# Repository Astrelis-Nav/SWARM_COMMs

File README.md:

# SWARM_COMMs
A modular communication system for underwater ROV swarms and multi-node vehicle systems.

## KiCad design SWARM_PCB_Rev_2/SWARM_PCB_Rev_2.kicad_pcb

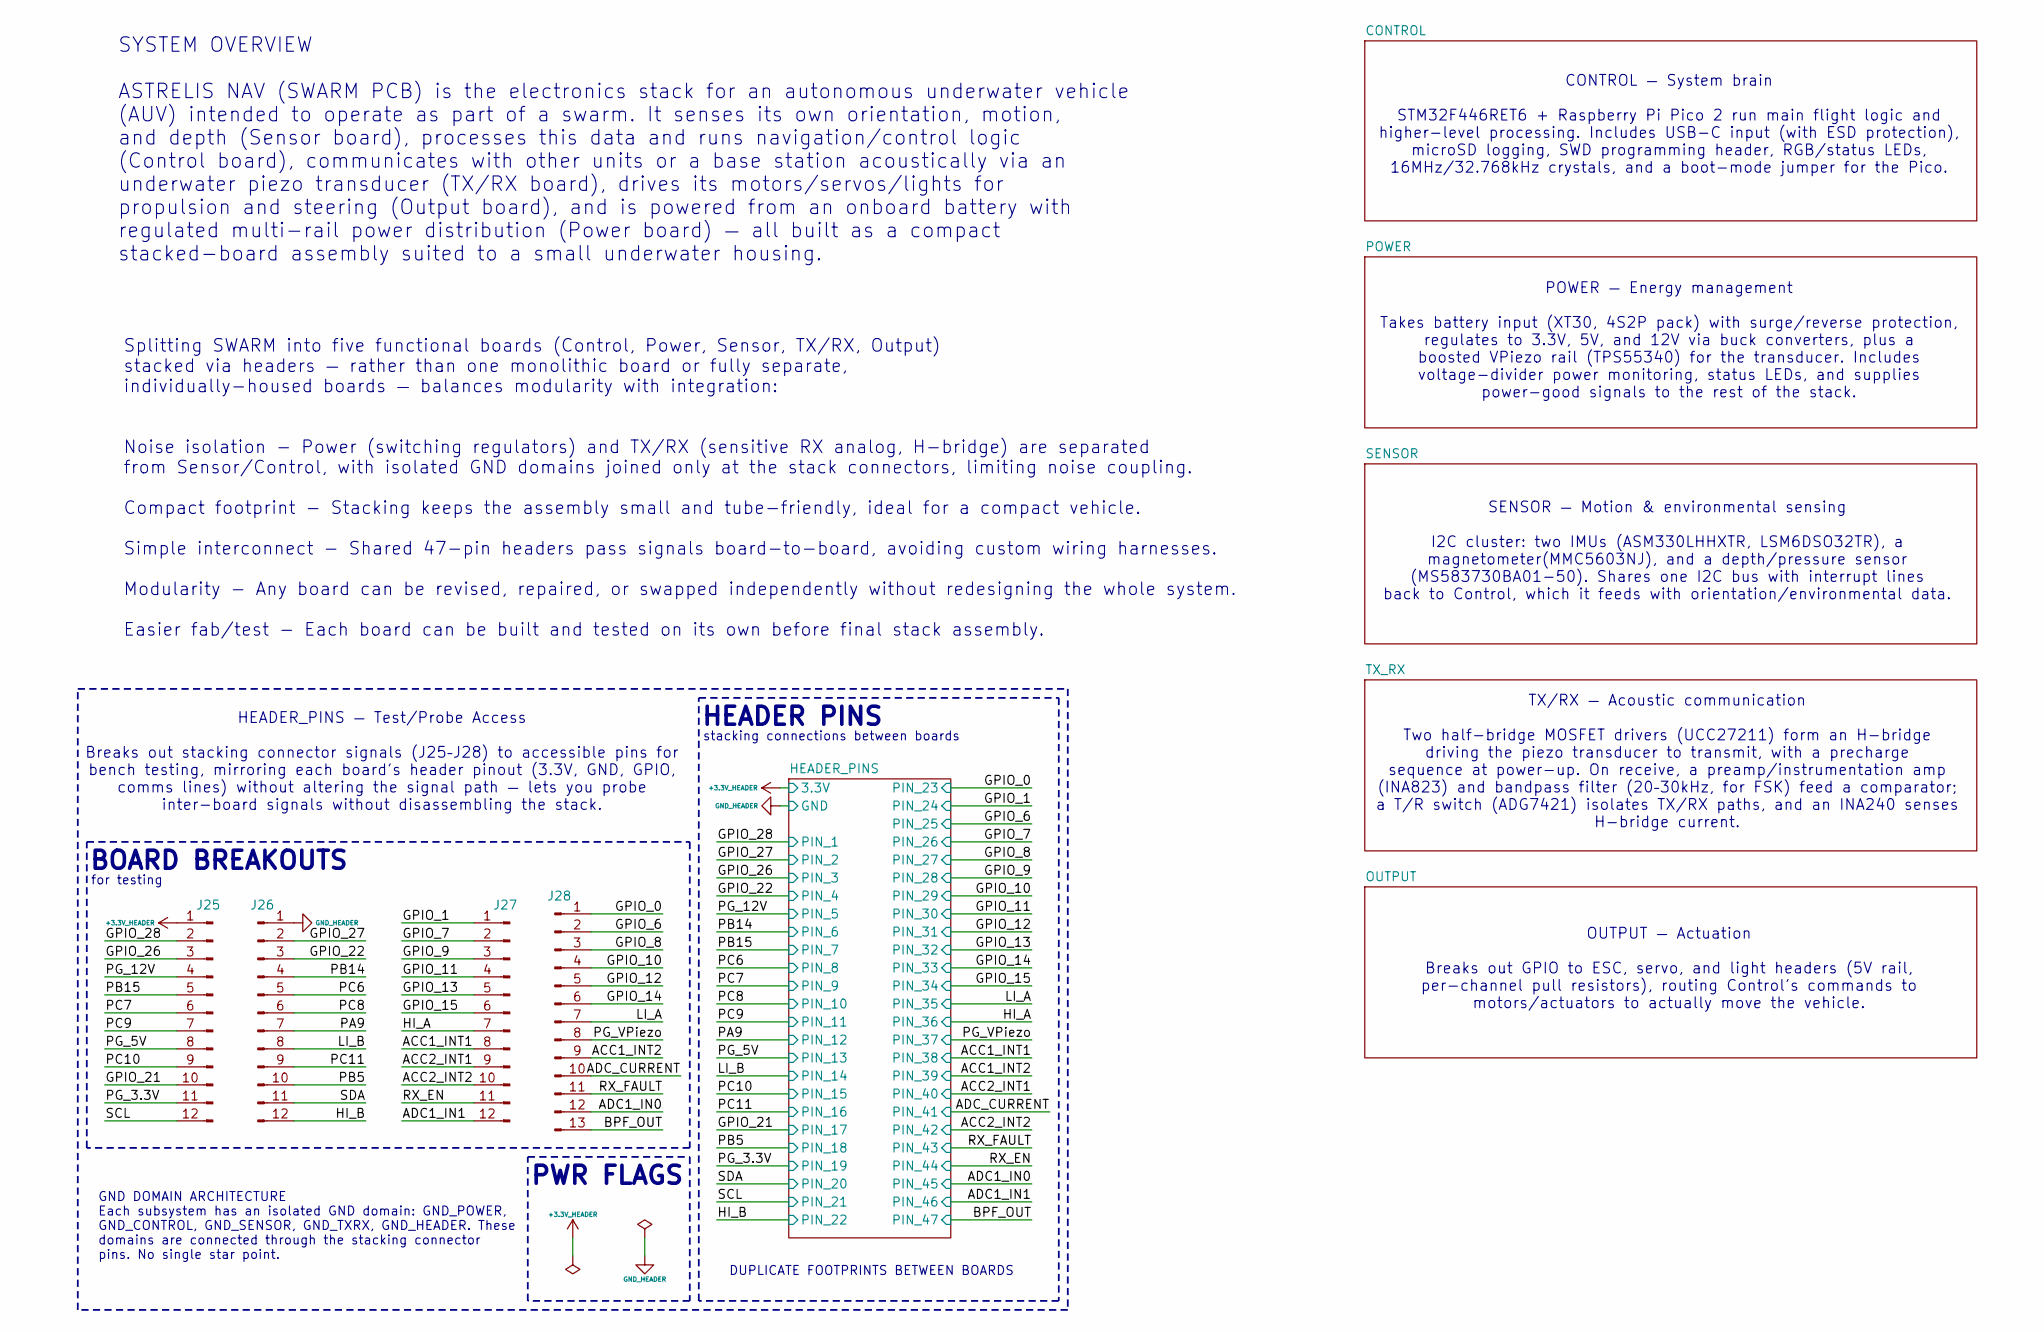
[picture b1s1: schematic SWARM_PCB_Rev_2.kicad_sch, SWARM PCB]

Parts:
J25, J26, J27: Conn_01x12_Pin; PinSocket_1x12_P2.54mm_Vertical
J28: Conn_01x13_Pin; PinSocket_1x13_P2.54mm_Vertical

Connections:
+3.3V_HEADER: J25.1; also elsewhere on the board
/ACC1_INT1: J27.8; also elsewhere on the board
/ACC1_INT2: J28.9; also elsewhere on the board
/ACC2_INT1: J27.9; also elsewhere on the board
/ACC2_INT2: J27.10; also elsewhere on the board
/ADC1_IN0: J28.12; also elsewhere on the board
/ADC1_IN1: J27.12; also elsewhere on the board
/ADC_CURRENT: J28.10; also elsewhere on the board
/BPF_OUT: J28.13; also elsewhere on the board
/GPIO_0: J28.1; also elsewhere on the board
/GPIO_1: J27.1; also elsewhere on the board
/GPIO_6: J28.2; also elsewhere on the board
/GPIO_7: J27.2; also elsewhere on the board
/GPIO_8: J28.3; also elsewhere on the board
/GPIO_9: J27.3; also elsewhere on the board
/GPIO_10: J28.4; also elsewhere on the board
/GPIO_11: J27.4; also elsewhere on the board
/GPIO_12: J28.5; also elsewhere on the board
/GPIO_13: J27.5; also elsewhere on the board
/GPIO_14: J28.6; also elsewhere on the board
/GPIO_15: J27.6; also elsewhere on the board
/GPIO_21: J25.10; also elsewhere on the board
/GPIO_22: J26.3; also elsewhere on the board
/GPIO_26: J25.3; also elsewhere on the board
/GPIO_27: J26.2; also elsewhere on the board
/GPIO_28: J25.2; also elsewhere on the board
/HI_A: J27.7; also elsewhere on the board
/HI_B: J26.12; also elsewhere on the board
/LI_A: J28.7; also elsewhere on the board
/LI_B: J26.8; also elsewhere on the board
/PA9: J26.7; also elsewhere on the board
/PB5: J26.10; also elsewhere on the board
/PB14: J26.4; also elsewhere on the board
/PB15: J25.5; also elsewhere on the board
/PC6: J26.5; also elsewhere on the board
/PC7: J25.6; also elsewhere on the board
/PC8: J26.6; also elsewhere on the board
/PC9: J25.7; also elsewhere on the board
/PC10: J25.9; also elsewhere on the board
/PC11: J26.9; also elsewhere on the board
/PG_3.3V: J25.11; also elsewhere on the board
/PG_5V: J25.8; also elsewhere on the board
/PG_12V: J25.4; also elsewhere on the board
/PG_VPiezo: J28.8; also elsewhere on the board
/RX_EN: J27.11; also elsewhere on the board
/RX_FAULT: J28.11; also elsewhere on the board
/SCL: J25.12; also elsewhere on the board
/SDA: J26.11; also elsewhere on the board
GND_HEADER: J26.1; also elsewhere on the board

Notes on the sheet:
SYSTEM OVERVIEW ASTRELIS NAV (SWARM PCB) is the electronics stack for an autonomous underwater vehicle (AUV) intended to operate as part of a swarm. It senses its own orientation, motion, and depth (Sensor board), processes this data and runs navigation/control logic (Control board), communicates w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
for testing
DUPLICATE FOOTPRINTS BETWEEN BOARDS
HEADER_PINS — Test/Probe Access Breaks out stacking connector signals (J25–J28) to accessible pins for bench testing, mirroring each board's header pinout (3.3V, GND, GPIO, comms lines) without altering the signal path — lets you probe inter-board signals without disassembling the stack.
SENSOR — Motion & environmental sensing I2C cluster: two IMUs (ASM330LHHXTR, LSM6DSO32TR), a magnetometer(MMC5603NJ), and a depth/pressure sensor (MS583730BA01-50). Shares one I2C bus with interrupt lines back to Control, which it feeds with orientation/environmental data.
Splitting SWARM into five functional boards (Control, Power, Sensor, TX/RX, Output) stacked via headers — rather than one monolithic board or fully separate, individually-housed boards — balances modularity with integration: Noise isolation - Power (switching regulators) and TX/RX (sensitive RX ana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
POWER — Energy management Takes battery input (XT30, 4S2P pack) with surge/reverse protection, regulates to 3.3V, 5V, and 12V via buck converters, plus a boosted VPiezo rail (TPS55340) for the transducer. Includes voltage-divider power monitoring, status LEDs, and supplies power-good signals to the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
stacking connections between boards
BOARD BREAKOUTS
GND DOMAIN ARCHITECTURE Each subsystem has an isolated GND domain: GND_POWER, GND_CONTROL, GND_SENSOR, GND_TXRX, GND_HEADER. These domains are connected through the stacking connector pins. No single star point.
OUTPUT — Actuation Breaks out GPIO to ESC, servo, and light headers (5V rail, per-channel pull resistors), routing Control's commands to motors/actuators to actually move the vehicle.
CONTROL — System brain STM32F446RET6 + Raspberry Pi Pico 2 run main flight logic and higher-level processing. Includes USB-C input (with ESD protection), microSD logging, SWD programming header, RGB/status LEDs, 16MHz/32.768kHz crystals, and a boot-mode jumper for the Pico.
TX/RX — Acoustic communication Two half-bridge MOSFET drivers (UCC27211) form an H-bridge driving the piezo transducer to transmit, with a precharge sequence at power-up. On receive, a preamp/instrumentation amp (INA823) and bandpass filter (20–30kHz, for FSK) feed a comparator; a T/R switch (ADG74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
HEADER PINS
PWR FLAGS

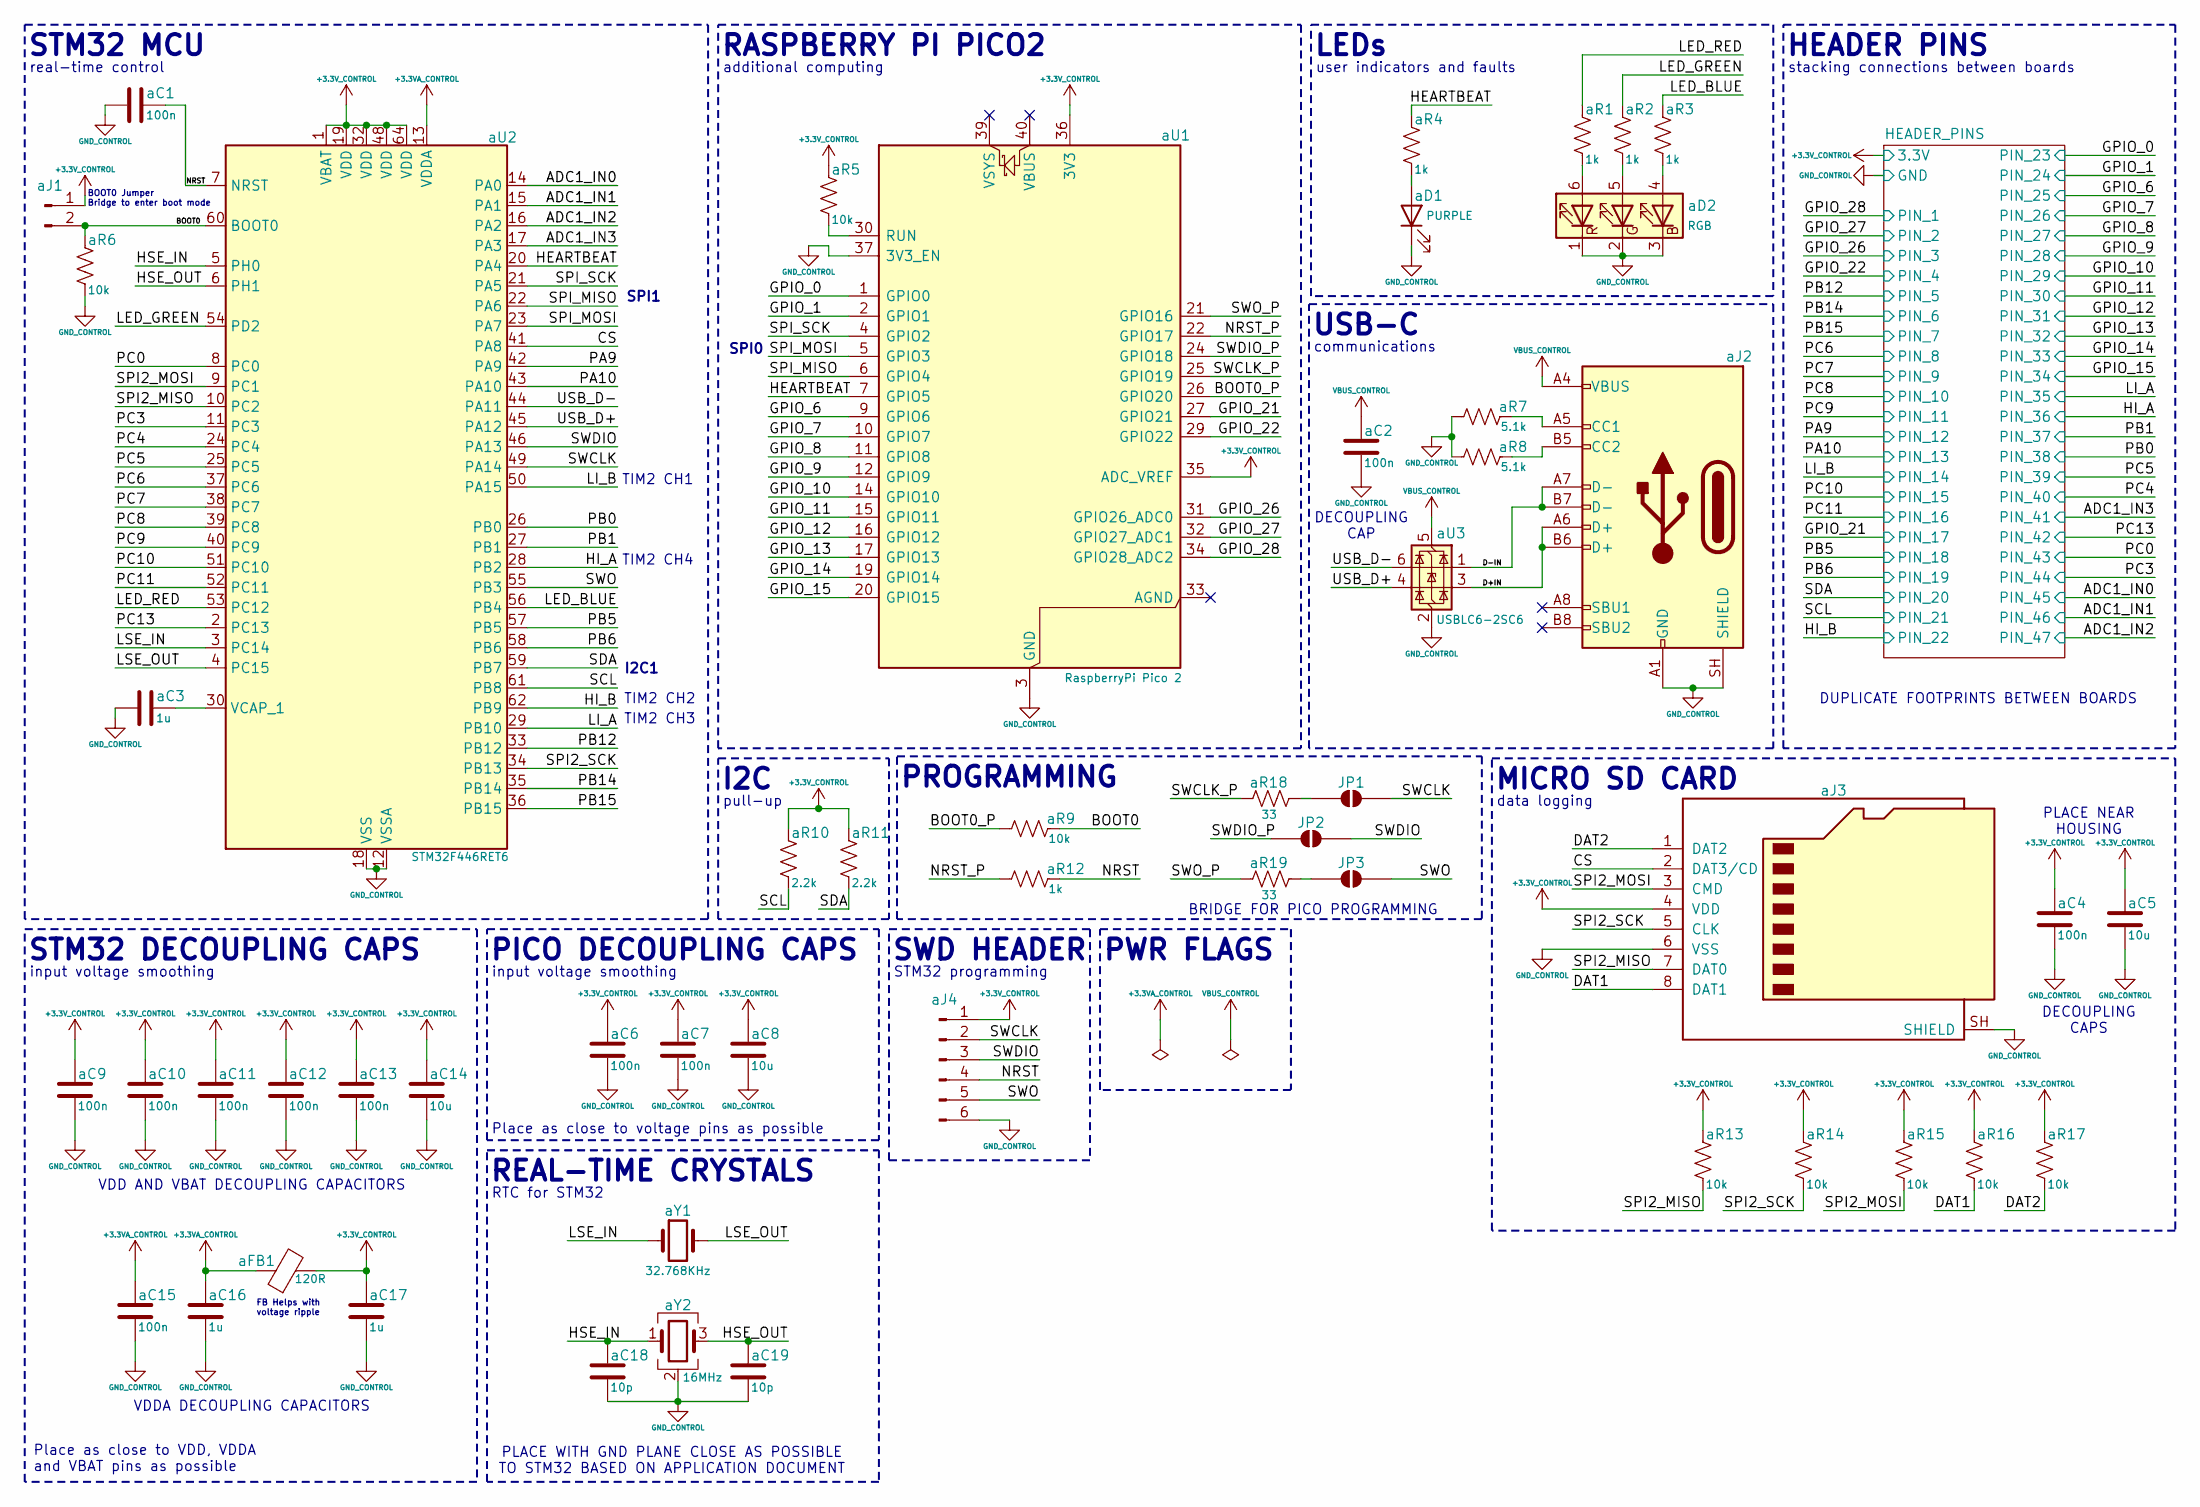
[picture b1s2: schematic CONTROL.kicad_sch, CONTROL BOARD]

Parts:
JP1, JP2, JP3: SolderJumper_2_Open; SolderJumper-2_P1.3mm_Open_TrianglePad1.0x1.5mm
aC1, aC2, aC4, aC6, aC7, aC9, aC10, aC11, aC12, aC13, aC15: 100n; C_0603_1608Metric; MPN GRM188R71C104KA01D
aC3: 1u; C_0603_1608Metric; MPN GRM188R60J105KE15D
aC5, aC8, aC14: 10u; C_0603_1608Metric; MPN GRM188R60J106ME47D
aC16, aC17: 1u; C_0603_1608Metric; MPN GRM188R61A105KA61D
aC18, aC19: 10p; C_0603_1608Metric; MPN GRM1885C1H100JA01D
aD1: PURPLE; LED_JE2835_CRW
aD2: RGB; LED_RGB_PLCC-6
aFB1: 120R; R_0603_1608Metric; MPN BLM18BD121SN1D
aJ1: Conn_01x02_Pin; PinHeader_1x02_P1.00mm_Vertical
aJ2: USB_C_Receptacle_USB2.0_16P; USB_C_Receptacle_GCT_USB4085; MPN USB4085-GF-A
aJ3: Micro_SD_Card; AMPHENOL_1140084168; MPN 1140084168
aJ4: Conn_01x06_Pin; PinHeader_1x06_P1.00mm_Vertical
aR1, aR2, aR3, aR4, aR12: 1k; R_0603_1608Metric; MPN RC0603FR-071KL
aR5, aR6, aR9, aR13, aR14, aR15, aR16, aR17: 10k; R_0603_1608Metric; MPN RC0603FR-0710KL
aR7, aR8: 5.1k; R_0603_1608Metric; MPN RC0603FR-075K1L
aR10, aR11: 2.2k; R_0603_1608Metric; MPN RC0603FR-074K7L
aR18, aR19: 33; R_0603_1608Metric; MPN RC0603FR-0733RL
aU1: RaspberryPi Pico 2; RaspberryPi_Pico_SMD; MPN SC0918
aU2: STM32F446RET6; LQFP-64_10x10mm_P0.5mm; MPN STM32F446RET6
aU3: USBLC6-2SC6; SOT-23-6; MPN USBLC6-2SC6
aY1: 32.768KHz; Crystal_SMD_MicroCrystal_CM9V-T1A-2Pin_1.6x1.0mm; MPN CM9V-T1A-32.768KDZB-UT
aY2: 16MHz; Crystal_SMD_SeikoEpson_FA238-4Pin_3.2x2.5mm; MPN FA-238 16.0000MB

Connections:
+3.3VA_CONTROL: aC15.2, aC16.2, aFB1.1, aU2.13 (VDDA)
+3.3V_CONTROL: aC4.2, aC5.2, aC6.2, aC7.2, aC8.2, aC9.2, aC10.2, aC11.2, aC12.2, aC13.2, aC14.2, aC17.2, aFB1.2, aJ1.1, aJ3.4 (VDD), aJ4.1, aR5.2, aR10.2, aR11.2, aR13.2, aR14.2, aR15.2, aR16.2, aR17.2, aU1.35 (ADC_VREF), aU1.36 (3V3), aU2.1 (VBAT), aU2.19 (VDD), aU2.32 (VDD), aU2.48 (VDD), aU2.64 (VDD); also elsewhere on the board
/CONTROL/ADC1_IN0: aU2.14 (PA0); also elsewhere on the board
/CONTROL/ADC1_IN1: aU2.15 (PA1); also elsewhere on the board
/CONTROL/ADC1_IN2: aU2.16 (PA2); also elsewhere on the board
/CONTROL/ADC1_IN3: aU2.17 (PA3); also elsewhere on the board
/CONTROL/BOOT0: aJ1.2, aR6.2, aR9.1, aU2.60 (BOOT0)
/CONTROL/BOOT0_P: aR9.2, aU1.26 (GPIO20)
/CONTROL/CS: aJ3.2 (DAT3/CD), aU2.41 (PA8)
/CONTROL/D+IN: aJ2.A6 (D+), aJ2.B6 (D+), aU3.3 (I/O2)
/CONTROL/D-IN: aJ2.A7 (D-), aJ2.B7 (D-), aU3.1 (I/O1)
/CONTROL/DAT1: aJ3.8 (DAT1), aR16.1
/CONTROL/DAT2: aJ3.1 (DAT2), aR17.1
/CONTROL/GPIO_0: aU1.1 (GPIO0); also elsewhere on the board
/CONTROL/GPIO_1: aU1.2 (GPIO1); also elsewhere on the board
/CONTROL/GPIO_6: aU1.9 (GPIO6); also elsewhere on the board
/CONTROL/GPIO_7: aU1.10 (GPIO7); also elsewhere on the board
/CONTROL/GPIO_8: aU1.11 (GPIO8); also elsewhere on the board
/CONTROL/GPIO_9: aU1.12 (GPIO9); also elsewhere on the board
/CONTROL/GPIO_10: aU1.14 (GPIO10); also elsewhere on the board
/CONTROL/GPIO_11: aU1.15 (GPIO11); also elsewhere on the board
/CONTROL/GPIO_12: aU1.16 (GPIO12); also elsewhere on the board
/CONTROL/GPIO_13: aU1.17 (GPIO13); also elsewhere on the board
/CONTROL/GPIO_14: aU1.19 (GPIO14); also elsewhere on the board
/CONTROL/GPIO_15: aU1.20 (GPIO15); also elsewhere on the board
/CONTROL/GPIO_21: aU1.27 (GPIO21); also elsewhere on the board
/CONTROL/GPIO_22: aU1.29 (GPIO22); also elsewhere on the board
/CONTROL/GPIO_26: aU1.31 (GPIO26_ADC0); also elsewhere on the board
/CONTROL/GPIO_27: aU1.32 (GPIO27_ADC1); also elsewhere on the board
/CONTROL/GPIO_28: aU1.34 (GPIO28_ADC2); also elsewhere on the board
/CONTROL/HEARTBEAT: aR4.2, aU1.7 (GPIO5), aU2.20 (PA4)
/CONTROL/HI_A: aU2.28 (PB2); also elsewhere on the board
/CONTROL/HI_B: aU2.62 (PB9); also elsewhere on the board
/CONTROL/HSE_IN: aC18.2, aU2.5 (PH0), aY2.1
/CONTROL/HSE_OUT: aC19.2, aU2.6 (PH1), aY2.3
/CONTROL/LED_BLUE: aR3.2, aU2.56 (PB4)
/CONTROL/LED_GREEN: aR2.2, aU2.54 (PD2)
/CONTROL/LED_RED: aR1.2, aU2.53 (PC12)
/CONTROL/LI_A: aU2.29 (PB10); also elsewhere on the board
/CONTROL/LI_B: aU2.50 (PA15); also elsewhere on the board
/CONTROL/LSE_IN: aU2.3 (PC14), aY1.1
/CONTROL/LSE_OUT: aU2.4 (PC15), aY1.2
/CONTROL/NRST: aC1.2, aJ4.4, aR12.1, aU2.7 (NRST)
/CONTROL/NRST_P: aR12.2, aU1.22 (GPIO17)
/CONTROL/PA9: aU2.42 (PA9); also elsewhere on the board
/CONTROL/PA10: aU2.43 (PA10); also elsewhere on the board
/CONTROL/PB0: aU2.26 (PB0); also elsewhere on the board
/CONTROL/PB1: aU2.27 (PB1); also elsewhere on the board
/CONTROL/PB5: aU2.57 (PB5); also elsewhere on the board
/CONTROL/PB6: aU2.58 (PB6); also elsewhere on the board
/CONTROL/PB12: aU2.33 (PB12); also elsewhere on the board
/CONTROL/PB14: aU2.35 (PB14); also elsewhere on the board
/CONTROL/PB15: aU2.36 (PB15); also elsewhere on the board
/CONTROL/PC0: aU2.8 (PC0); also elsewhere on the board
/CONTROL/PC3: aU2.11 (PC3); also elsewhere on the board
/CONTROL/PC4: aU2.24 (PC4); also elsewhere on the board
/CONTROL/PC5: aU2.25 (PC5); also elsewhere on the board
/CONTROL/PC6: aU2.37 (PC6); also elsewhere on the board
/CONTROL/PC7: aU2.38 (PC7); also elsewhere on the board
/CONTROL/PC8: aU2.39 (PC8); also elsewhere on the board
/CONTROL/PC9: aU2.40 (PC9); also elsewhere on the board
/CONTROL/PC10: aU2.51 (PC10); also elsewhere on the board
/CONTROL/PC11: aU2.52 (PC11); also elsewhere on the board
/CONTROL/PC13: aU2.2 (PC13); also elsewhere on the board
/CONTROL/SCL: aR10.1, aU2.61 (PB8); also elsewhere on the board
/CONTROL/SDA: aR11.1, aU2.59 (PB7); also elsewhere on the board
/CONTROL/SPI2_MISO: aJ3.7 (DAT0), aR13.1, aU2.10 (PC2)
/CONTROL/SPI2_MOSI: aJ3.3 (CMD), aR15.1, aU2.9 (PC1)
/CONTROL/SPI2_SCK: aJ3.5 (CLK), aR14.1, aU2.34 (PB13)
/CONTROL/SPI_MISO: aU1.6 (GPIO4), aU2.22 (PA6)
/CONTROL/SPI_MOSI: aU1.5 (GPIO3), aU2.23 (PA7)
/CONTROL/SPI_SCK: aU1.4 (GPIO2), aU2.21 (PA5)
/CONTROL/SWCLK: JP1.2 (B), aJ4.2, aU2.49 (PA14)
/CONTROL/SWCLK_P: aR18.2, aU1.25 (GPIO19)
/CONTROL/SWDIO: JP2.2 (B), aJ4.3, aU2.46 (PA13)
/CONTROL/SWDIO_P: JP2.1 (A), aU1.24 (GPIO18)
/CONTROL/SWO: JP3.2 (B), aJ4.5, aU2.55 (PB3)
/CONTROL/SWO_P: aR19.2, aU1.21 (GPIO16)
/CONTROL/USB_D+: aU2.45 (PA12), aU3.4 (I/O2)
/CONTROL/USB_D-: aU2.44 (PA11), aU3.6 (I/O1)
GND_CONTROL: aC1.1, aC2.1, aC3.1, aC4.1, aC5.1, aC6.1, aC7.1, aC8.1, aC9.1, aC10.1, aC11.1, aC12.1, aC13.1, aC14.1, aC15.1, aC16.1, aC17.1, aC18.1, aC19.1, aD1.1 (K), aD2.1 (RK), aD2.2 (GK), aD2.3 (BK), aJ2.A1 (GND), aJ2.A12 (GND), aJ2.B1 (GND), aJ2.B12 (GND), aJ2.SH (SHIELD), aJ3.6 (VSS), aJ3.SH (SHIELD), aJ4.6, aR6.1, aR7.2, aR8.2, aU1.3 (GND), aU1.8 (GND), aU1.13 (GND), aU1.18 (GND), aU1.23 (GND), aU1.28 (GND), aU1.37 (3V3_EN), aU1.38 (GND), aU2.12 (VSSA), aU2.18 (VSS), aU2.31 (VSS), aU2.47 (VSS), aU2.63 (VSS), aU3.2 (GND), aY2.2 (G), aY2.4 (G); also elsewhere on the board
unnamed: JP1.1 (A), aR18.1
unnamed: JP3.1 (A), aR19.1
unnamed: aD1.2 (A), aR4.1
unnamed: aD2.4 (BA), aR3.1
unnamed: aD2.5 (GA), aR2.1
unnamed: aD2.6 (RA), aR1.1
unnamed: aJ2.A5 (CC1), aR7.1
unnamed: aJ2.B5 (CC2), aR8.1
unnamed: aR5.1, aU1.30 (RUN)
unnamed: aC3.2, aU2.30 (VCAP_1)
VBUS_CONTROL: aC2.2, aJ2.A4 (VBUS), aJ2.A9 (VBUS), aJ2.B4 (VBUS), aJ2.B9 (VBUS), aU3.5 (VBUS)

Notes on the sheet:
DECOUPLING CAP
VDDA DECOUPLING CAPACITORS
user indicators and faults
real-time control
DECOUPLING CAPS
Place as close to voltage pins as possible
data logging
FB Helps with voltage ripple
STM32 MCU
BOOT0 Jumper Bridge to enter boot mode
SPI1
BRIDGE FOR PICO PROGRAMMING
STM32 programming
communications
Place as close to VDD, VDDA and VBAT pins as possible
USB-C
I2C
STM32 DECOUPLING CAPS
TIM2 CH3
PLACE WITH GND PLANE CLOSE AS POSSIBLE TO STM32 BASED ON APPLICATION DOCUMENT
PLACE NEAR HOUSING
SWD HEADER
additional computing
PWR FLAGS
input voltage smoothing
RTC for STM32
LEDs
TIM2 CH4
VDD AND VBAT DECOUPLING CAPACITORS
SPI0
HEADER PINS
I2C1
MICRO SD CARD
TIM2 CH2
PROGRAMMING
pull-up
RASPBERRY PI PICO2
stacking connections between boards
PICO DECOUPLING CAPS
TIM2 CH1

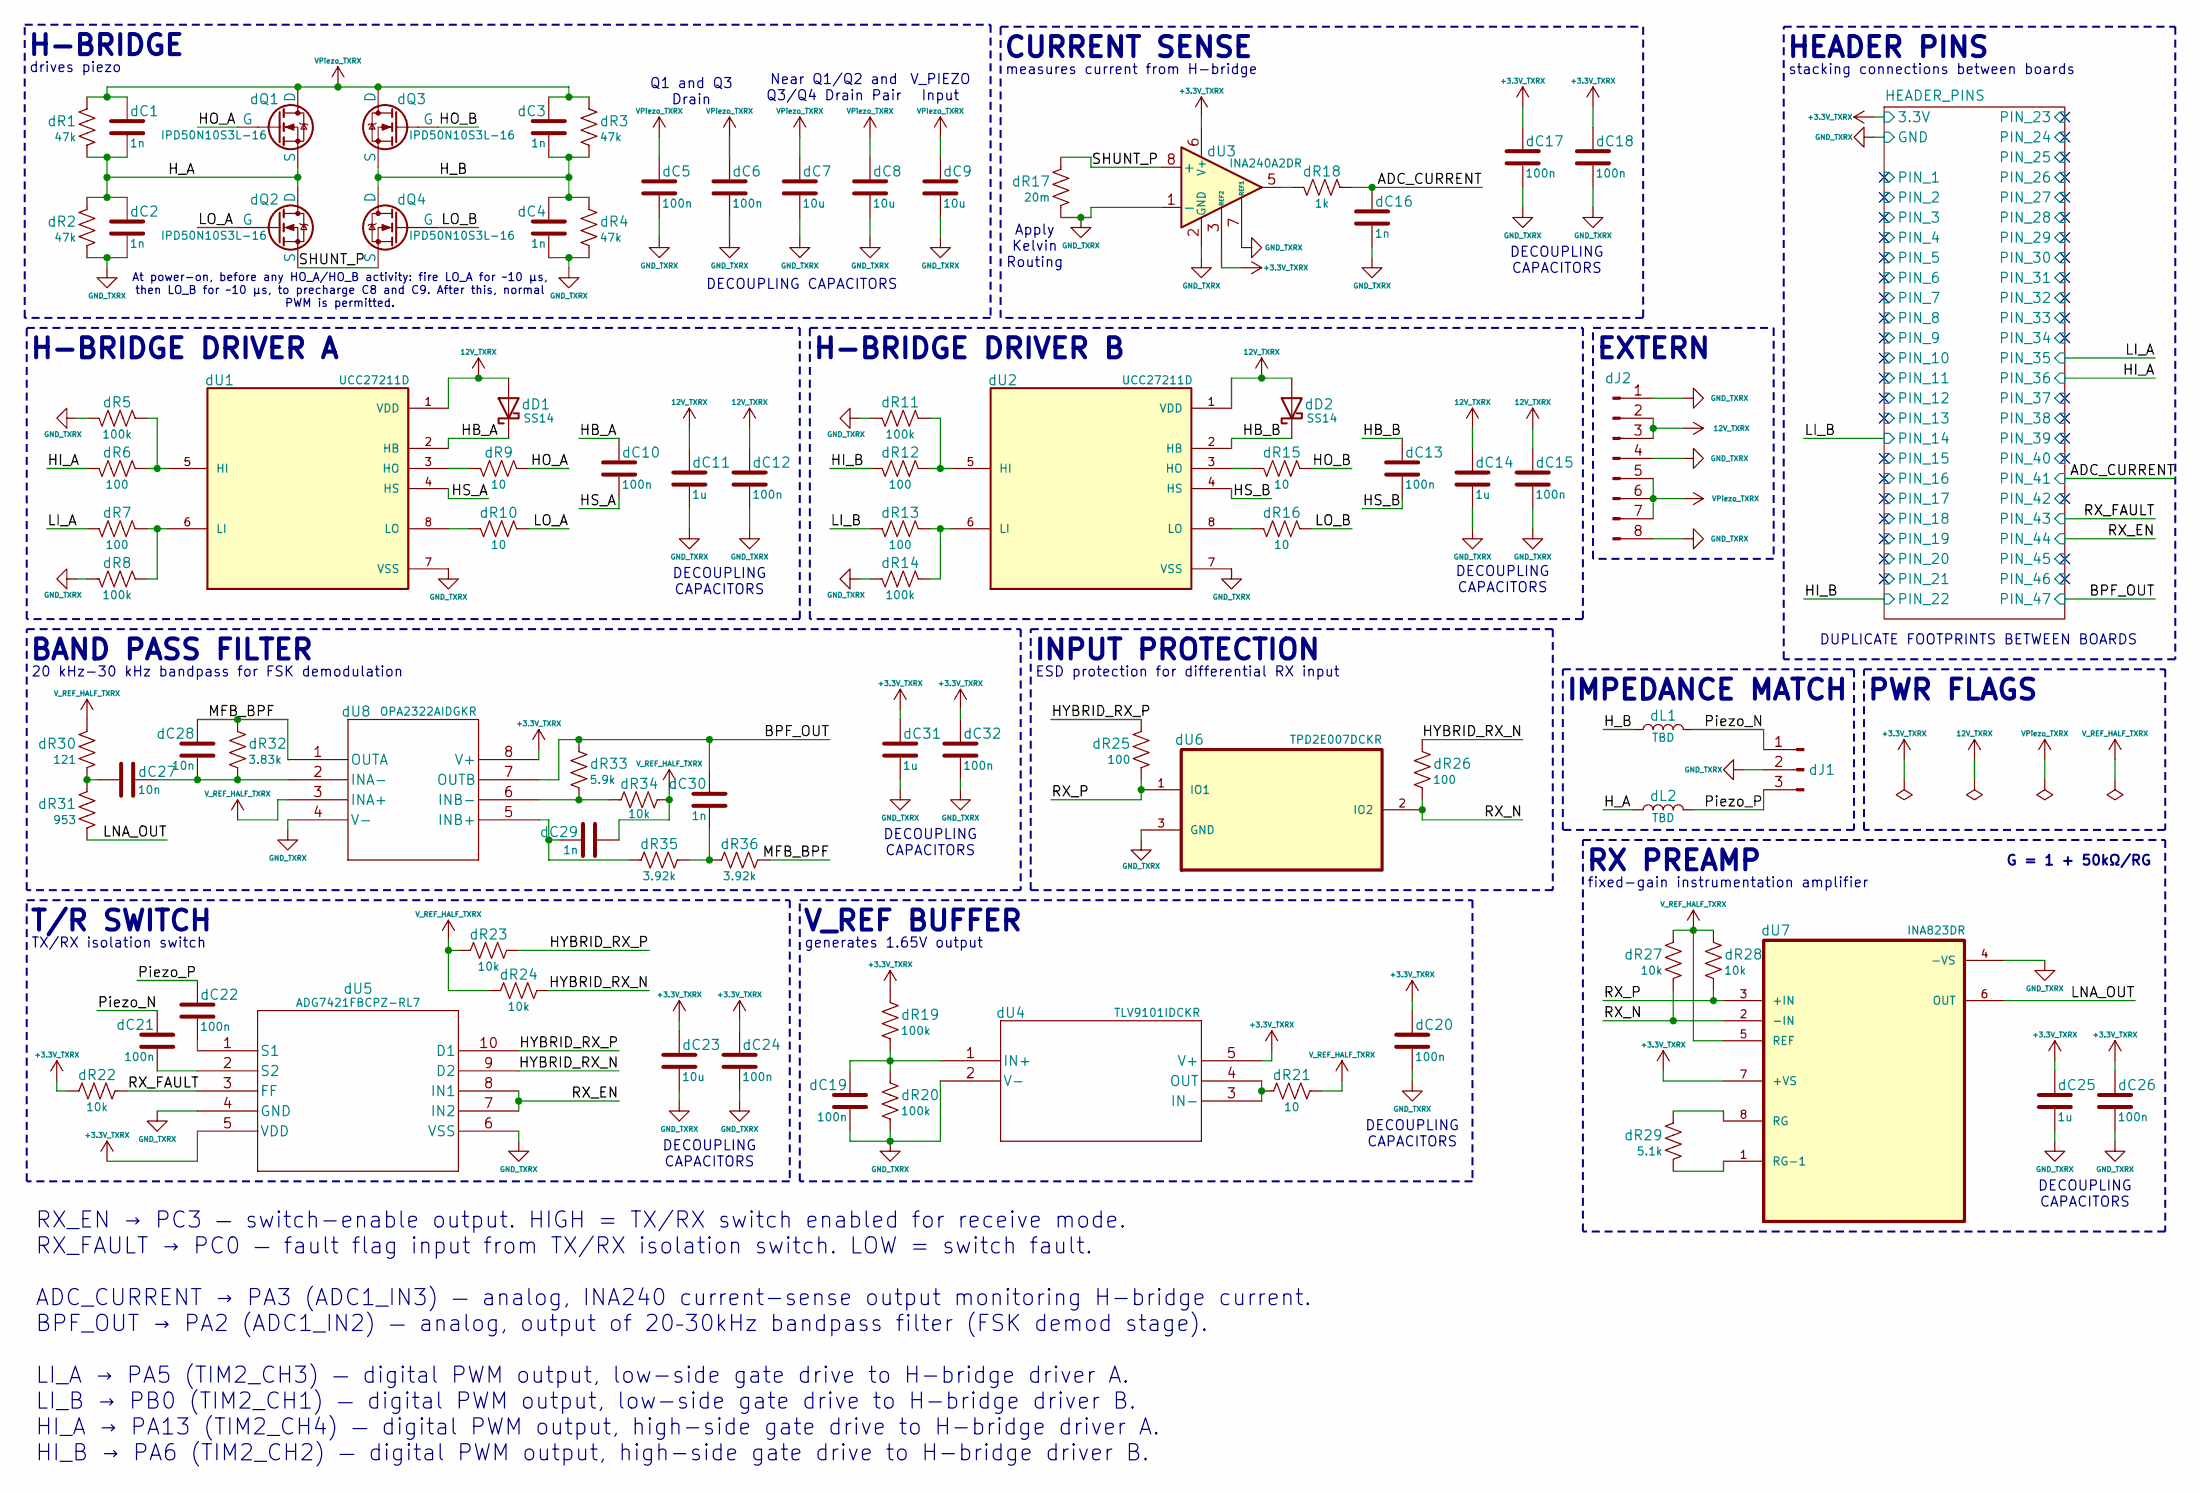
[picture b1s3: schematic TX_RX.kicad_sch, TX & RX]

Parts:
dC1, dC2, dC3, dC4, dC16, dC29, dC30: 1n; C_0603_1608Metric; MPN GRM1885C1H102JA01D
dC5, dC6, dC10, dC12, dC13, dC15, dC17, dC18, dC19, dC20, dC21, dC22, dC24, dC26, dC32: 100n; C_0603_1608Metric; MPN GRM188R71C104KA01D
dC7, dC8, dC9: 10u; C_1210_3225Metric; MPN GRM32ER71H106KA12
dC11, dC14: 1u; C_0805_2012Metric; MPN GRM21BR61A105KA73L
dC23: 10u; C_0805_2012Metric_Pad1.18x1.45mm_HandSolder; MPN GRM21BR61A106KE18L
dC25, dC31: 1u; C_0603_1608Metric; MPN GRM188R61A105KA61D
dC27, dC28: 10n; C_0603_1608Metric; MPN GRM188R71H103KA01D
dD1, dD2: SS14; D_SMA
dJ1: Conn_01x03_Pin; JST_XH_B3B-XH-AM_1x03_P2.50mm_Vertical; MPN B3B-XH-AM
dJ2: Conn_01x08_Pin; JST_PH_B8B-PH-SM4-TB_1x08-1MP_P2.00mm_Vertical; MPN B8B-PH-SM4-TB(LF)(SN)
dL1, dL2: TBD; L_Panasonic_PCC-M0630M
dQ1, dQ2, dQ3, dQ4: IPD50N10S3L-16; TO-252-2; MPN IPD50N10S3L-16
dR1, dR2, dR3, dR4: 47k; R_0603_1608Metric; MPN RC0603FR-0747KL
dR5, dR8, dR11, dR14, dR19, dR20: 100k; R_0603_1608Metric; MPN RC0603FR-07100KL
dR6, dR7, dR12, dR13, dR25, dR26: 100; R_0603_1608Metric; MPN RC0603FR-07100RL
dR9, dR10, dR15, dR16, dR21: 10; R_0603_1608Metric; MPN RC0603FR-0710RL
dR17: 20m; R_2512_6332Metric; MPN WSL2512R0200FEA
dR18: 1k; R_0603_1608Metric; MPN RC0603FR-071KL
dR22, dR23, dR24, dR27, dR28, dR34: 10k; R_0603_1608Metric; MPN RC0603FR-0710KL
dR29: 5.1k; R_0603_1608Metric; MPN RC0603FR-075K1L
dR30: 121; R_0603_1608Metric; MPN RC0603FR-07121RL
dR31: 953; R_0603_1608Metric; MPN RC0603FR-07953RL
dR32: 3.83k; R_0603_1608Metric; MPN RC0603FR-073K83L
dR33: 5.9k; R_0603_1608Metric; MPN RC0603FR-075K9L
dR35, dR36: 3.92k; R_0603_1608Metric; MPN RC0603FR-073K92L
dU1, dU2: UCC27211D; SOIC127P599X175-8N; PARTREV F; DigiKey_Part_Number 296-30016-5-ND
dU3: INA240A2DR; SOIC-8_3.9x4.9mm_P1.27mm; MPN INA240A2DR
dU4: TLV9101IDCKR; SC70-5_DCK_TEX; MPN TLV9101IDCKR
dU5: ADG7421FBCPZ-RL7; CP-10-16_ADI; MPN ADG7421FBCPZ-RL7
dU6: TPD2E007DCKR; DCK3; MPN TPD2E007DCKR
dU7: INA823DR; SOIC127P599X175-8N; MPN INA823DR
dU8: OPA2322AIDGKR; DGK8; MPN OPA2322AIDGKR

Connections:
12V_TXRX: dC11.2, dC12.2, dC14.2, dC15.2, dD1.2 (A), dD2.2 (A), dJ2.2, dJ2.3, dU1.1 (VDD), dU2.1 (VDD)
+3.3V_TXRX: dC17.2, dC18.2, dC20.2, dC23.2, dC24.2, dC25.2, dC26.2, dC31.2, dC32.2, dR19.2, dR22.2, dU3.3 (REF2), dU3.6 (V+), dU4.5 (V+), dU5.5 (VDD), dU7.7 (+VS), dU8.8 (V+); also elsewhere on the board
/TX_RX/ADC_CURRENT: dC16.2, dR18.1; also elsewhere on the board
/TX_RX/BPF_OUT: dC30.2, dR33.2, dU8.7 (OUTB); also elsewhere on the board
/TX_RX/HB_A: dC10.2, dD1.1 (K), dU1.2 (HB)
/TX_RX/HB_B: dC13.2, dD2.1 (K), dU2.2 (HB)
/TX_RX/HI_A: dR6.2; also elsewhere on the board
/TX_RX/HI_B: dR12.2; also elsewhere on the board
/TX_RX/HS_A: dC10.1, dU1.4 (HS)
/TX_RX/HS_B: dC13.1, dU2.4 (HS)
/TX_RX/HYBRID_RX_N: dR24.1, dR26.2, dU5.9 (D2)
/TX_RX/HYBRID_RX_P: dR23.1, dR25.2, dU5.10 (D1)
/TX_RX/LI_A: dR7.2; also elsewhere on the board
/TX_RX/LI_B: dR13.2; also elsewhere on the board
/TX_RX/LNA_OUT: dR31.1, dU7.6 (OUT)
/TX_RX/MFB_BPF: dC28.2, dR32.2, dR36.1, dU8.1 (OUTA)
/TX_RX/Piezo_N: dC21.2, dJ1.1, dL1.2
/TX_RX/Piezo_P: dC22.2, dJ1.3, dL2.2
/TX_RX/RX_EN: dU5.7 (IN2), dU5.8 (IN1); also elsewhere on the board
/TX_RX/RX_FAULT: dR22.1, dU5.3 (FF); also elsewhere on the board
/TX_RX/RX_N: dR26.1, dR27.1, dU6.2 (IO2), dU7.2 (-IN)
/TX_RX/RX_P: dR25.1, dR28.1, dU6.1 (IO1), dU7.3 (+IN)
/TX_RX/SHUNT_P: dQ2.3 (S), dQ4.3 (S), dR17.2, dU3.8 (+)
GND_TXRX: dC2.1, dC4.1, dC5.1, dC6.1, dC7.1, dC8.1, dC9.1, dC11.1, dC12.1, dC14.1, dC15.1, dC16.1, dC17.1, dC18.1, dC19.1, dC20.1, dC23.1, dC24.1, dC25.1, dC26.1, dC31.1, dC32.1, dJ1.2, dJ2.1, dJ2.4, dJ2.8, dR2.1, dR4.1, dR5.2, dR8.2, dR11.2, dR14.2, dR17.1, dR20.1, dU1.7 (VSS), dU2.7 (VSS), dU3.1 (-), dU3.2 (GND), dU3.4 (GND), dU3.7 (REF1), dU4.2 (V-), dU5.4 (GND), dU5.6 (VSS), dU6.3 (GND), dU7.4 (-VS), dU8.4 (V-); also elsewhere on the board
unnamed: dC27.2, dR30.1, dR31.2
unnamed: dC30.1, dR35.1, dR36.2
unnamed: dR18.2, dU3.5
unnamed: dR5.1, dR6.1, dU1.5 (HI)
unnamed: dR9.2, dU1.3 (HO)
unnamed: dR7.1, dR8.1, dU1.6 (LI)
unnamed: dR10.2, dU1.8 (LO)
unnamed: dR11.1, dR12.1, dU2.5 (HI)
unnamed: dR15.2, dU2.3 (HO)
unnamed: dR13.1, dR14.1, dU2.6 (LI)
unnamed: dR16.2, dU2.8 (LO)
unnamed: dC19.2, dR19.1, dR20.2, dU4.1 (IN+)
unnamed: dR21.2, dU4.3 (IN-), dU4.4 (OUT)
unnamed: dC22.1, dU5.1 (S1)
unnamed: dC21.1, dU5.2 (S2)
unnamed: dR29.2, dU7.8 (RG)
unnamed: dR29.1, dU7.1 (RG-1)
unnamed: dC27.1, dC28.1, dR32.1, dU8.2 (INA-)
unnamed: dC29.1, dR35.2, dU8.5 (INB+)
unnamed: dR33.1, dR34.2, dU8.6 (INB-)
V_REF_HALF_TXRX: dC29.2, dR21.1, dR23.2, dR24.2, dR27.2, dR28.2, dR30.2, dR34.1, dU7.5 (REF), dU8.3 (INA+)

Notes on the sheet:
DECOUPLING CAPACITORS
INPUT PROTECTION
H-BRIDGE DRIVER B
stacking connections between boards
20 kHz-30 kHz bandpass for FSK demodulation
drives piezo
V_PIEZO Input
Near Q1/Q2 and Q3/Q4 Drain Pair
CURRENT SENSE
G = 1 + 50kΩ/RG
EXTERN
Q1 and Q3 Drain
ESD protection for differential RX input
BAND PASS FILTER
T/R SWITCH
PWR FLAGS
IMPEDANCE MATCH
Apply Kelvin Routing
TX/RX isolation switch
DUPLICATE FOOTPRINTS BETWEEN BOARDS
H-BRIDGE DRIVER A
V_REF BUFFER
RX_EN → PC3 — switch-enable output. HIGH = TX/RX switch enabled for receive mode. RX_FAULT → PC0 — fault flag input from TX/RX isolation switch. LOW = switch fault. ADC_CURRENT → PA3 (ADC1_IN3) — analog, INA240 current-sense output monitoring H-bridge current. BPF_OUT → PA2 (ADC1_IN2) — analog, out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
H-BRIDGE
generates 1.65V output
HEADER PINS
RX PREAMP
measures current from H-bridge
fixed-gain instrumentation amplifier
DECOUPLING CAPACITORS
At power-on, before any HO_A/HO_B activity: fire LO_A for ~10 µs, then LO_B for ~10 µs, to precharge C8 and C9. After this, normal PWM is permitted.
